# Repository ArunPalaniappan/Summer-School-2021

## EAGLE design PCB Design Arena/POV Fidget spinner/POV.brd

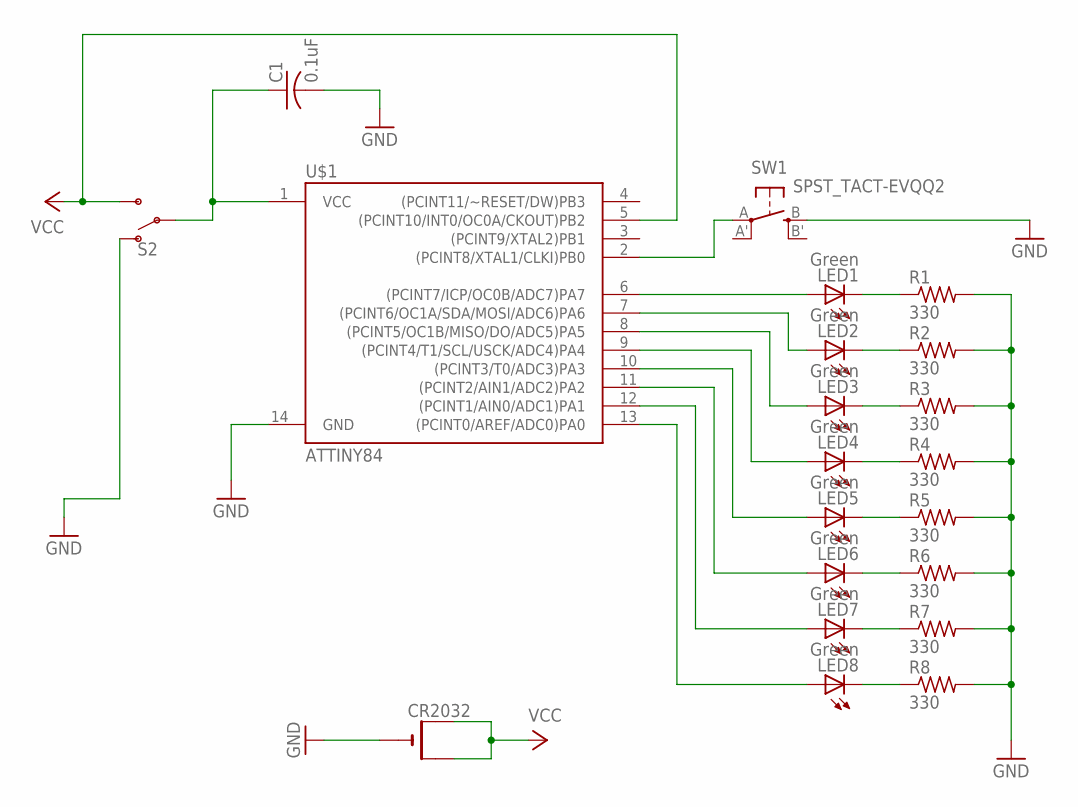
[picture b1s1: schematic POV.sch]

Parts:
C1: 0.1uF; C0805
CR2032: CR2032SMT; CR2032-SMD
LED1, LED2, LED3, LED4, LED5, LED6, LED7, LED8: Green; CHIP-LED0805
R1, R2, R3, R4, R5, R6, R7, R8: 330; M0805
S2: SWITCH-SPDT-SMD-AYZ0202; SWITCH_DPDT_SMD_AYZ0202
SW1: SPST_TACT-EVQQ2; EVQ-Q2
U$1: ATTINY84; SO14

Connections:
GND: C1.2, CR2032.-, R1.2, R2.2, R3.2, R4.2, R5.2, R6.2, R7.2, R8.2, S2.1 (O), SW1.B (S), U$1.14 (GND)
unnamed: LED1.A, U$1.6 ((PCINT7/ICP/OC0B/ADC7)PA7)
unnamed: LED1.C, R1.1
unnamed: LED2.C, R2.1
unnamed: LED3.C, R3.1
unnamed: LED4.C, R4.1
unnamed: LED5.C, R5.1
unnamed: LED6.C, R6.1
unnamed: LED7.C, R7.1
unnamed: LED8.C, R8.1
unnamed: LED2.A, U$1.7 ((PCINT6/OC1A/SDA/MOSI/ADC6)PA6)
unnamed: LED3.A, U$1.8 ((PCINT5/OC1B/MISO/DO/ADC5)PA5)
unnamed: LED4.A, U$1.9 ((PCINT4/T1/SCL/USCK/ADC4)PA4)
unnamed: LED5.A, U$1.10 ((PCINT3/T0/ADC3)PA3)
unnamed: LED6.A, U$1.11 ((PCINT2/AIN1/ADC2)PA2)
unnamed: LED7.A, U$1.12 ((PCINT1/AIN0/ADC1)PA1)
unnamed: LED8.A, U$1.13 ((PCINT0/AREF/ADC0)PA0)
unnamed: C1.1, S2.2, U$1.1 (VCC)
unnamed: SW1.A, U$1.2 ((PCINT8/XTAL1/CLKI)PB0)
VCC: CR2032.+$1 (+), CR2032.+$2 (+1), S2.3 (S), U$1.5 ((PCINT10/INT0/OC0A/CKOUT)PB2)

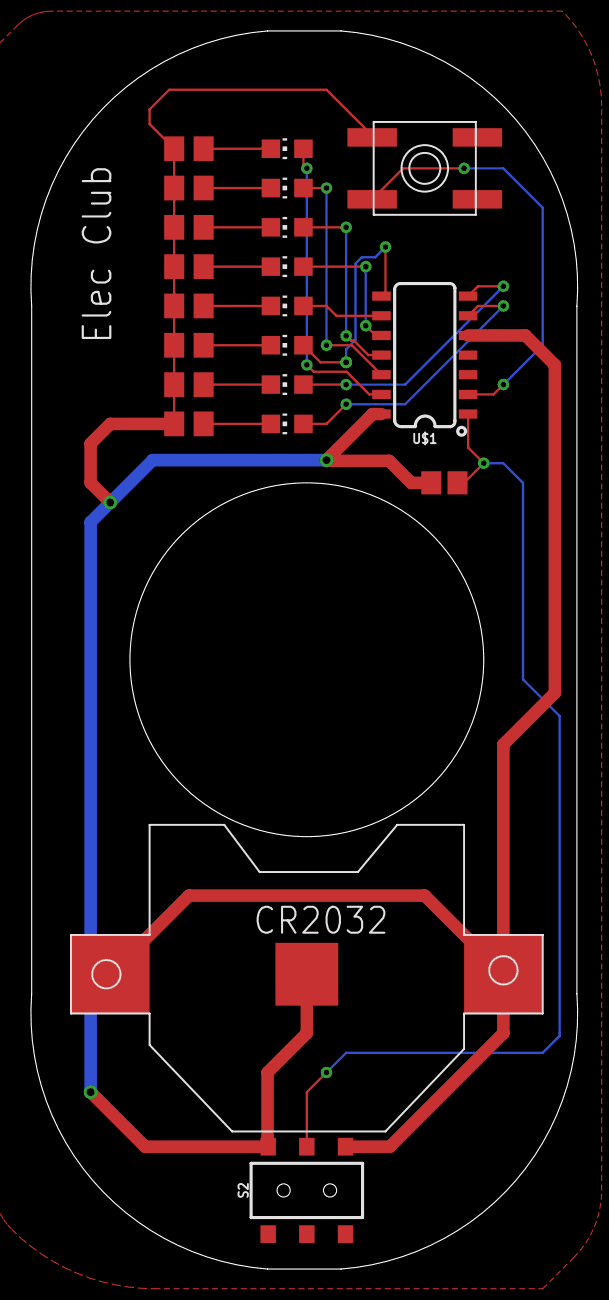
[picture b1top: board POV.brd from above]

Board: 2 copper layers, 35.3 x 80.0 mm, 21 parts (0 on the bottom side), 20 nets.

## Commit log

2021-10-10 Create h
2021-10-10 Added Resources

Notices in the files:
parts and their libraries:
SparkFun-Switches: Licensing: Creative Commons ShareAlike 4.0 International - https://creativecommons.org/licenses/by-sa/4.0
